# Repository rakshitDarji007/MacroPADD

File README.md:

# MacroPADD
macropad
Hey Guys,
This is my first time doing anything with hardware, I was super excited to learn and the guide was very helpful. But I basically made a macroopad.

# Schematic: 

# PCB:

# Case:

# BOM:
Seeed XIAO RP2040
MX-Style switches x 6
Keycaps x 6
Rotary Encoder x 1 
0.91 inch OLED displays x 1 
M3x16mm screws x 4
M3x5mx4mm heatset inserts x 4
3d Printed Case

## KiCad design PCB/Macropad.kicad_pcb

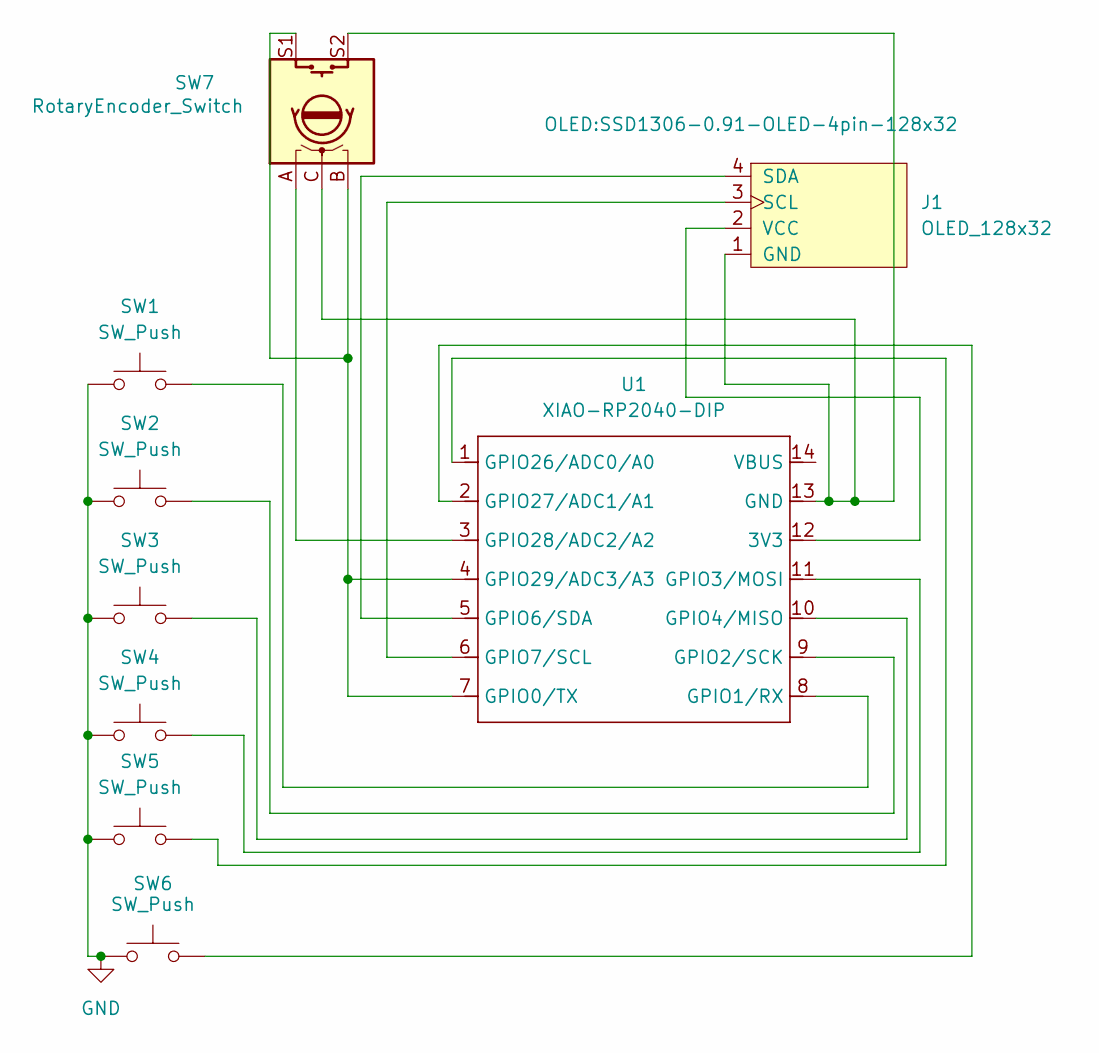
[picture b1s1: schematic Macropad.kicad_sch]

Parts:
J1: OLED_128x32; SSD1306-0.91-OLED-4pin-128x32
SW1, SW2, SW3, SW4, SW5, SW6: SW_Push; SW_Cherry_MX_1.00u_PCB
SW7: RotaryEncoder_Switch; RotaryEncoder_Alps_EC11E-Switch_Vertical_H20mm
U1: XIAO-RP2040-DIP

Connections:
GND: SW1.1, SW2.1, SW3.1, SW4.1, SW5.1, SW6.1
unnamed: J1.1 (GND), SW7.C, SW7.S2, U1.13 (GND)
unnamed: J1.3 (SCL), U1.6 (GPIO7/SCL)
unnamed: J1.4 (SDA), U1.5 (GPIO6/SDA)
unnamed: J1.2 (VCC), U1.12 (3V3)
unnamed: SW7.B, SW7.S1, U1.4 (GPIO29/ADC3/A3), U1.7 (GPIO0/TX)
unnamed: SW1.2, U1.8 (GPIO1/RX)
unnamed: SW2.2, U1.9 (GPIO2/SCK)
unnamed: SW4.2, U1.11 (GPIO3/MOSI)
unnamed: SW3.2, U1.10 (GPIO4/MISO)
unnamed: SW5.2, U1.1 (GPIO26/ADC0/A0)
unnamed: SW6.2, U1.2 (GPIO27/ADC1/A1)
unnamed: SW7.A, U1.3 (GPIO28/ADC2/A2)

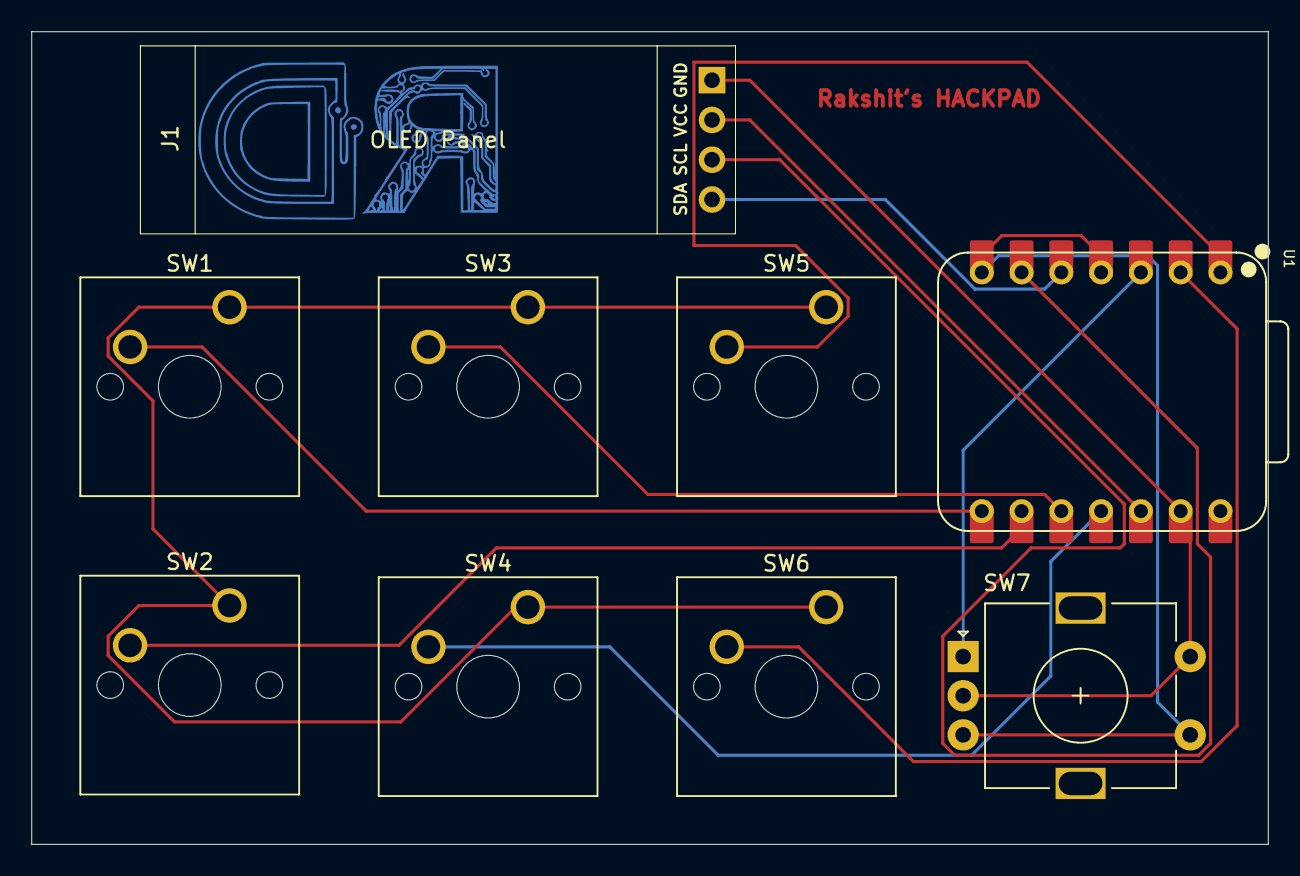
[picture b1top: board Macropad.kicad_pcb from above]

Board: 2 copper layers, 79.0 x 51.9 mm, 9 parts (0 on the bottom side), 13 nets.

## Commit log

2025-05-24 Create test
2025-05-24 PCB files
2025-05-24 CAD Design
2025-05-24 Production
2025-05-24 Productions files
